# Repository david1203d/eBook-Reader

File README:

# 📘 Ebook Reader cu ESP32-C6

Acest proiect este un **Ebook Reader portabil**, cu consum redus, bazat pe **ESP32-C6** și ecran **E-Paper**, ideal pentru lectură prelungită.  
Dispozitivul citește fișiere `.txt` de pe un card **microSD** și permite navigarea cu **butoane fizice**, având alimentare din **baterie Li-Po** și opțional monitorizare a nivelului acesteia.

---

## 📦 Bill of Materials (BOM)

| Componentă           | Model/Tip                  | Link comandă | Datasheet     |
|----------------------|----------------------------|--------------|----------------|
| Microcontroller      | ESP32-C6                   | Mouser       | [ESP32-C6](#)  |
| Ecran                | E-Paper Display 2.9"       | Comet        | [GDEH029A1](#) |
| Cart Reader          | MicroSD SPI module         | Mouser       | [Modul SD](#)  |
| Senzor de mediu      | BME688                     | Mouser       | [BME688](#)    |
| RTC                  | DS3231SN                   | Mouser       | [DS3231](#)    |
| Battery Monitor      | MAX17048                   | Mouser       | [MAX17048](#)  |
| Flash extern         | W25Q512JV (64MB)           | Mouser       | [W25Q512JV](#) |
| Regulator tensiune   | MCP1826S-3302E/DB          | Mouser       | [MCP1826](#)   |
| BMS                  | TP4056                     | Comet        | [TP4056](#)    |
| Butoane              | Tactile Switches           | Comet        | [SKQG](#)      |

---

## ⚙️ Funcționalitate Hardware

### 1. ESP32-C6
- Interfață principală: SPI, I2C, GPIO  
- Flash extern NOR (64MB) prin QSPI  
- UART pentru debug  
- Alimentare 3.3V prin LDO

### 2. E-Paper Display
- Alimentat prin EPD Power Driver (boost + FET)  
- Conectat prin SPI la ESP32-C6  
- Pini dedicați: DIN, CLK, CS, DC, RST, BUSY

### 3. Modul SD Card
- Interfață SPI  
- Stocare fișiere `.txt`

### 4. RTC DS3231SN
- I2C cu backup battery (CR2032)  
- Oră exactă cu temperatură compensată

### 5. Senzor BME688
- I2C – temperatură, presiune, umiditate, calitate aer  
- Util pentru monitorizare ambientală (opțional)

### 6. MAX17048
- Monitorizare nivel baterie prin I2C  
- Poate afișa procentul pe ecran

### 7. TP4056 Charging
- Încărcare Li-Po prin USB-C  
- Protecție la supradescărcare/supraincărcare

---

## 📌 Pini ESP32-C6 Utilizați

| Pin ESP32-C6 | Funcție hardware         | Componentă              |
|--------------|--------------------------|--------------------------|
| GPIO0        | I2C SCL                  | BME688, MAX17048, DS3231 |
| GPIO1        | I2C SDA                  | BME688, MAX17048, DS3231 |
| GPIO2        | SPI MOSI                | E-paper, SD, Flash       |
| GPIO3        | SPI MISO                | SD, Flash                |
| GPIO4        | SPI CLK                 | E-paper, SD, Flash       |
| GPIO5        | SPI CS (e-paper)        | E-paper                  |
| GPIO6        | SPI CS (SD card)        | SD Card                  |
| GPIO7        | SPI CS (Flash extern)   | W25Q512JV                |
| GPIO8        | GPIO Buton 1            | Pag. înainte             |
| GPIO9        | GPIO Buton 2            | Pag. înapoi              |
| GPIO10       | GPIO Buton 3            | Reset/Menu               |
| GPIO11       | UART TX                 | Debug UART               |
| GPIO12       | UART RX                 | Debug UART               |

---

## 🖼️ Design PCB & Randări

- **PCB**: 2 straturi, dimensiuni: `92.2mm x 67.2mm`  
- **Componente** poziționate compact pentru portabilitate  
- **Acces ușor** la card microSD, USB-C și butoane  
- **Protecție ESD** pe liniile USB și SPI  

## ✅ Alte Detalii Relevante

- **Mod Deep Sleep**: activat după 30s de inactivitate  
- **W25Q512JV Flash extern**: stocare rapidă pentru sute de cărți `.txt`  
- **Qwiic/Stemma QT header**: pentru expansiune cu alte periferice  
- **Test Pads**: depanare & validare semnal

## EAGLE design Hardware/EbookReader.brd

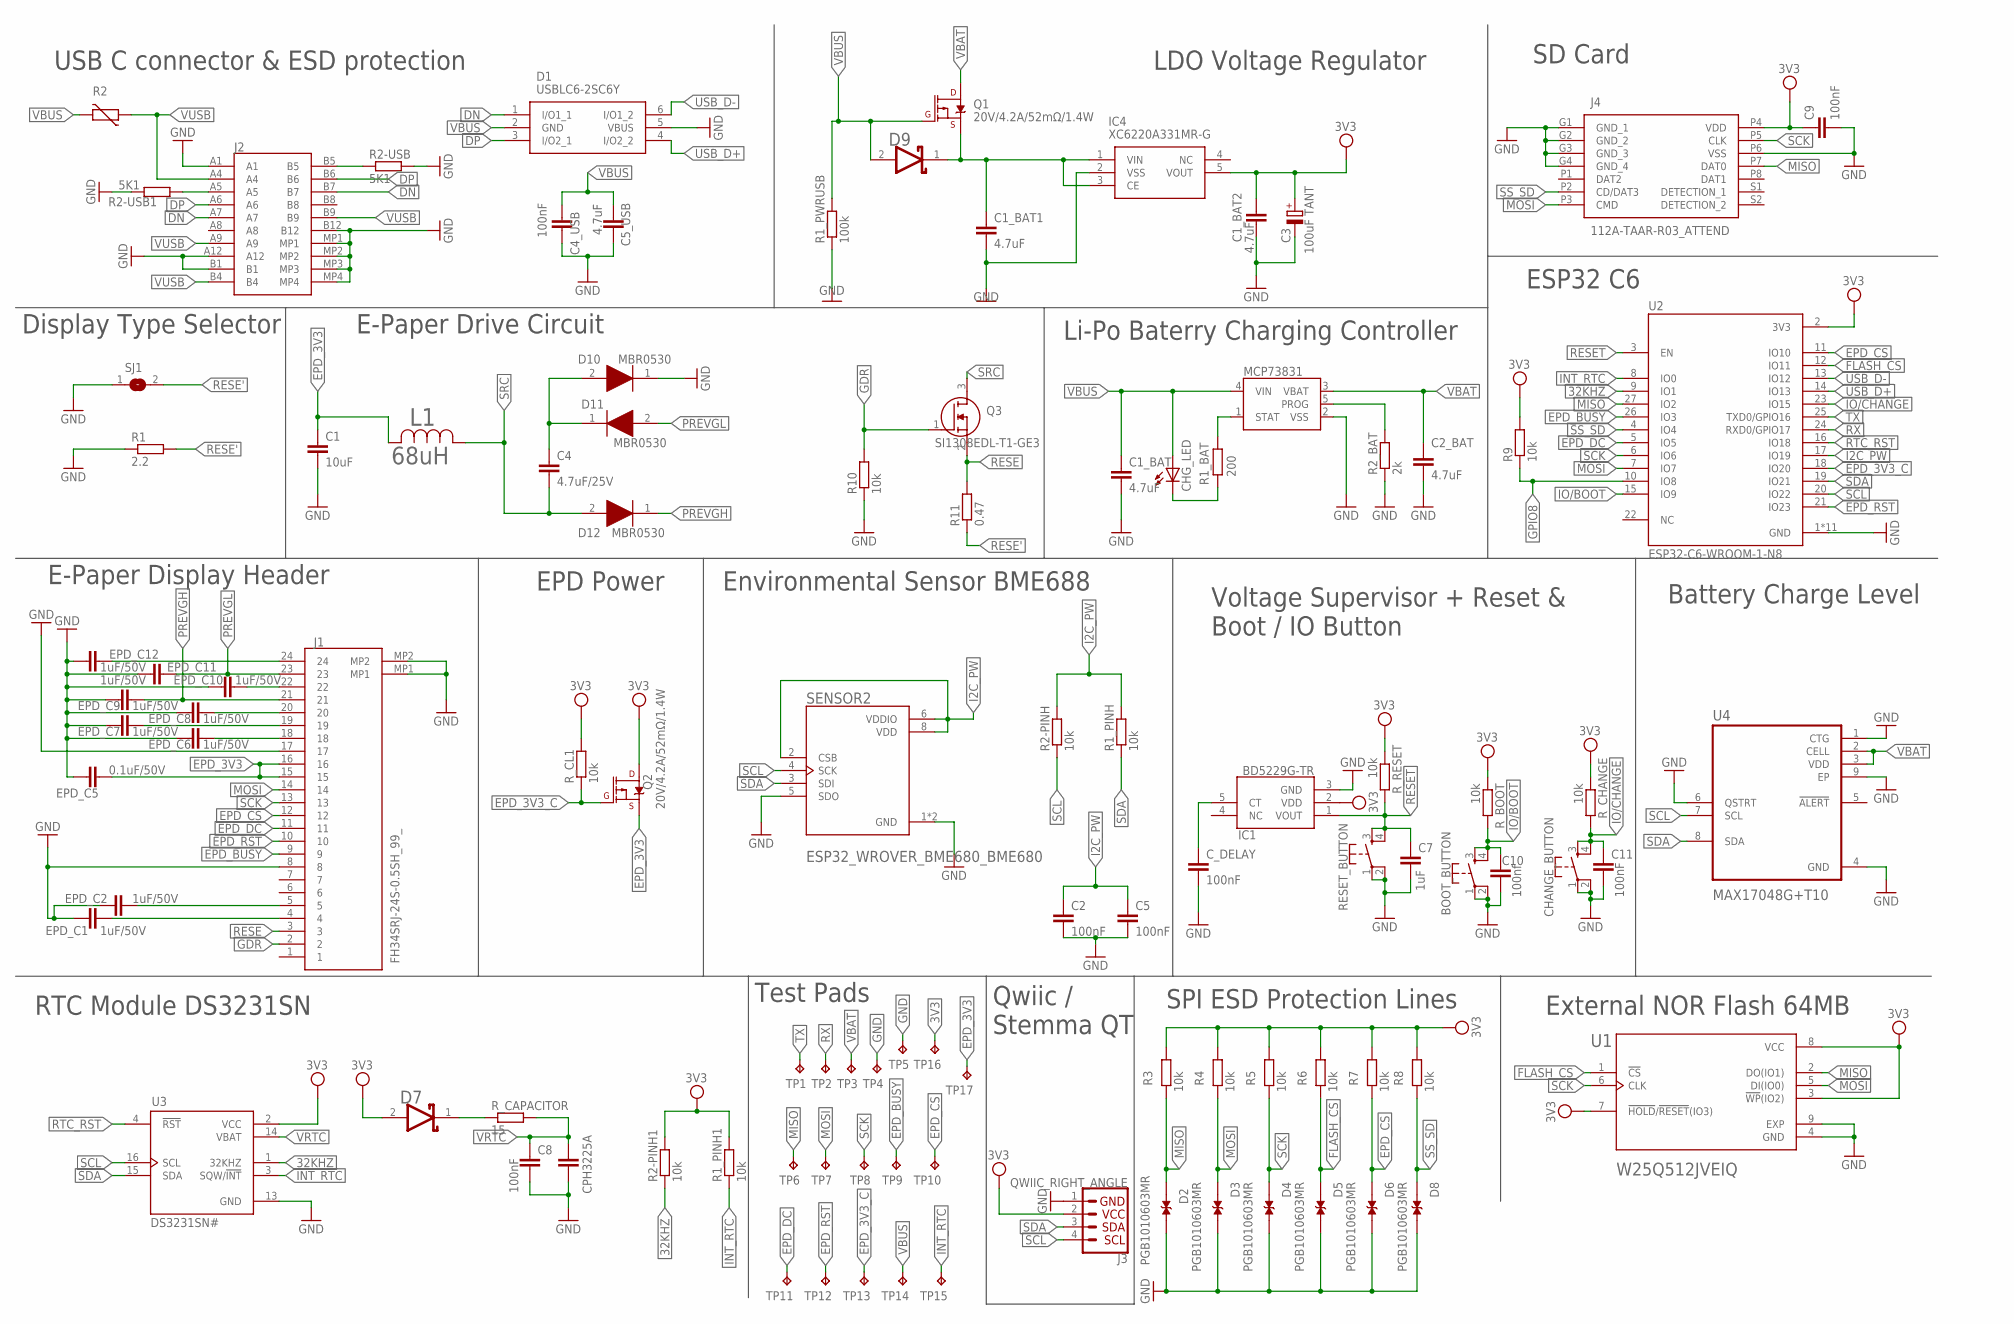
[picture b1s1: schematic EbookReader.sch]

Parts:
BOOT_BUTTON: BUTTON_CUSYOMV1; MYBUTTON
C1: 10uF; ESP32_WROVER_EAGLE-LTSPICE_C0402
C1_BAT, C1_BAT1, C1_BAT2, C2_BAT, C5_USB: 4.7uF; ESP32_WROVER_EAGLE-LTSPICE_C0402
C2, C4_USB, C5, C9, C11: 100nF; ESP32_WROVER_EAGLE-LTSPICE_C0402
C3: 100uF TANT; RCL_CT3528
C4: 4.7uF/25V; ESP32_WROVER_EAGLE-LTSPICE_C0402
C7: 1uF; ESP32_WROVER_EAGLE-LTSPICE_C0402
C8: 100nF; EAGLE-LTSPICE_C0402
C10: 100nf; ESP32_WROVER_EAGLE-LTSPICE_C0402
CHANGE_BUTTON: BUTTON_CUSYOMV1; MYBUTTON
CHG_LED: ADAFRUIT_LEDCHIP-LED0603; ADAFRUIT_CHIP-LED0603
CPH3225A: EAGLE-LTSPICE_CC0402; EAGLE-LTSPICE_C0402
C_DELAY: 100nF; ESP32_WROVER_EAGLE-LTSPICE_C0402
D1: USBLC6-2SC6Y; SOT95P280X145-6N
D2, D3, D4, D5, D6, D8: PGB1010603MR; DIOC1608X36N
D7, D9: ESP32_WROVER_AVX---SD0805S020S1R0_AVX_SD0805S020S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; ESP32_WROVER_AVX---SD0805S020S1R0_AVX_SD0805S020S1R0_0
D10, D11, D12: MBR0530; SOD3716X135N
EPD_C1, EPD_C2, EPD_C6, EPD_C7, EPD_C8, EPD_C9, EPD_C10, EPD_C11, EPD_C12: 1uF/50V; EAGLE-LTSPICE_C0402
EPD_C5: 0.1uF/50V; EAGLE-LTSPICE_C0402
IC1: BD5229G-TR; SOT95P280X125-5N
IC4: XC6220A331MR-G; SOT95P280X120-5N
J1: FH34SRJ-24S-0.5SH_99_; FH34SRJ24S05SH99
J2: SAMACSYS_PARTS_USB4110-GF-A; SAMACSYS_PARTS_USB4110GFA
J3: QWIIC_RIGHT_ANGLE; JST04_1MM_RA
J4: 112A-TAAR-R03_ATTEND; 112ATAARR03ATTEND
L1: 68uH; IND_4828-WE-TPC_WRE
MCP73831: ESP32_WROVER_SPARKFUN-IC-POWER_MCP73831; ESP32_WROVER_SPARKFUN-IC-POWER_SOT23-5
Q1, Q2: 20V/4.2A/52mΩ/1.4W; ESP32_WROVER_SPARKFUN-DISCRETESEMI_SOT23-3
Q3: SI1308EDL-T1-GE3; SOT65P210X110-3N
R1: 2.2; ESP32_WROVER_EAGLE-LTSPICE_R0402
R1_BAT: 200; ESP32_WROVER_EAGLE-LTSPICE_R0402
R1_PINH, R1_PINH1, R2-PINH, R2-PINH1, R3, R4, R5, R6, R7, R8, R9, R10: 10k; ESP32_WROVER_EAGLE-LTSPICE_R0402
R1_PWRUSB: 100k; ESP32_WROVER_EAGLE-LTSPICE_R0402
R2: ESP32C6_VARISTORCN1812; ESP32C6_VARISTOR_CT/CN1812
R2-USB, R2-USB1: 5K1; ESP32_WROVER_EAGLE-LTSPICE_R0402
R2_BAT: 2k; ESP32_WROVER_EAGLE-LTSPICE_R0402
R11: 0.47; ESP32_WROVER_EAGLE-LTSPICE_R0402
RESET_BUTTON: BUTTON_CUSYOMV1; MYBUTTON
R_BOOT: 10k; ESP32_WROVER_EAGLE-LTSPICE_R0402
R_CAPACITOR: 15; ESP32_WROVER_EAGLE-LTSPICE_R0402
R_CHANGE: 10k; ESP32_WROVER_EAGLE-LTSPICE_R0402
R_CL1: 10k; ESP32_WROVER_EAGLE-LTSPICE_R0402
R_RESET: 10k; ESP32_WROVER_EAGLE-LTSPICE_R0402
SENSOR2: ESP32_WROVER_BME680_BME680; ESP32_WROVER_BME680_PSON80P300X300X100-8N
SJ1: SJ
TP1, TP2, TP3, TP4, TP5, TP6, TP7, TP8, TP9, TP10, TP11, TP12, TP13, TP14, TP15, TP16, TP17: TPTP20R; TP20R
U1: W25Q512JVEIQ; SON127P600X800X80-9N
U2: ESP32-C6-WROOM-1-N8; XCVR_ESP32-C6-WROOM-1-N8
U3: DS3231SN#; SOIC127P1032X265-16N
U4: MAX17048G+T10; SON50P200X200X80-9N

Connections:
3V3: C1_BAT2.1, C3.+, C9.1, D7.2 (ANODE), IC1.2 (VDD), IC4.5 (VOUT), J3.2, J4.P4 (VDD), Q2.3 (D), R1_PINH1.2, R2-PINH1.2, R3.2, R4.2, R5.2, R6.2, R7.2, R8.2, R9.2, R_BOOT.1, R_CHANGE.1, R_CL1.2, R_RESET.1, TP16.TP, U1.3 (!WP!(IO2)), U1.7 (!HOLD!/!RESET!(IO3)), U1.8 (VCC), U2.2 (3V3), U3.2 (VCC)
32KHZ: R2-PINH1.1, U2.9 (IO1), U3.1 (32KHZ)
DN: D1.1 (I/O1_1), J2.A7, J2.B7
DP: D1.3 (I/O2_1), J2.A6, J2.B6
EPD_3V3: C1.1, EPD_C5.1, J1.15, J1.16, L1.2, Q2.2 (S), TP17.TP
EPD_3V3_C: Q2.1 (G), R_CL1.1, TP13.TP, U2.18 (IO20)
EPD_BUSY: J1.9, TP9.TP, U2.26 (IO3)
EPD_CS: D6.1, J1.12, R7.1, TP10.TP, U2.11 (IO10)
EPD_DC: J1.11, TP11.TP, U2.5 (IO5)
EPD_RST: J1.10, TP12.TP, U2.21 (IO23)
FLASH_CS: D5.1, R6.1, U1.1 (!CS), U2.12 (IO11)
GDR: J1.2, Q3.1 (G), R10.2
GND: BOOT_BUTTON.1, BOOT_BUTTON.2, C1.2, C1_BAT.2, C1_BAT1.2, C1_BAT2.2, C2.2, C2_BAT.2, C3.-, C4_USB.2, C5.2, C5_USB.2, C7.2, C8.2, C9.2, C10.2, C11.2, CHANGE_BUTTON.1, CHANGE_BUTTON.2, CPH3225A.2, C_DELAY.2, D1.5 (VBUS), D2.2, D3.2, D4.2, D5.2, D6.2, D8.2, D10.1 (K), EPD_C1.2, EPD_C2.2, EPD_C5.2, EPD_C6.2, EPD_C7.2, EPD_C8.2, EPD_C9.2, EPD_C10.2, EPD_C11.2, EPD_C12.2, IC1.3 (GND), IC4.2 (VSS), J1.8, J1.17, J1.MP1, J1.MP2, J2.A1, J2.A12, J2.B1, J2.B12, J2.MP1, J2.MP2, J2.MP3, J2.MP4, J3.1, J4.G1 (GND_1), J4.G2 (GND_2), J4.G3 (GND_3), J4.G4 (GND_4), J4.P6 (VSS), MCP73831.2 (VSS), R1.1, R1_PWRUSB.1, R2-USB.2, R2-USB1.1, R2_BAT.1, R10.1, RESET_BUTTON.1, RESET_BUTTON.2, SENSOR2.1 (GND), SENSOR2.5 (SDO), SENSOR2.7 (GND), SJ1.1, TP4.TP, TP5.TP, U1.4 (GND), U1.9 (EXP), U2.1 (GND), U2.28 (GND), U2.29_1 (GND), U2.29_2 (GND), U2.29_3 (GND), U2.29_4 (GND), U2.29_5 (GND), U2.29_6 (GND), U2.29_7 (GND), U2.29_8 (GND), U2.29_9 (GND), U3.13 (GND), U4.1 (CTG), U4.4 (GND), U4.6 (QSTRT), U4.9 (EP)
GPIO8: R9.1, U2.10 (IO8)
I2C_PW: C2.1, C5.1, R1_PINH.2, R2-PINH.2, SENSOR2.2 (CSB), SENSOR2.6 (VDDIO), SENSOR2.8 (VDD), U2.17 (IO19)
INT_RTC: R1_PINH1.1, TP15.TP, U2.8 (IO0), U3.3 (SQW/!INT)
IO/BOOT: BOOT_BUTTON.3, BOOT_BUTTON.4, C10.1, R_BOOT.2, U2.15 (IO9)
IO/CHANGE: C11.1, CHANGE_BUTTON.3, CHANGE_BUTTON.4, R_CHANGE.2, U2.23 (IO15)
MISO: D2.1, J4.P7 (DAT0), R3.1, TP6.TP, U1.2 (DO(IO1)), U2.27 (IO2)
MOSI: D3.1, J1.14, J4.P3 (CMD), R4.1, TP7.TP, U1.5 (DI(IO0)), U2.7 (IO7)
unnamed: J2.A5, R2-USB1.2
unnamed: EPD_C12.1, J1.24
unnamed: D7.1 (CATHODE), R_CAPACITOR.1
unnamed: EPD_C10.1, J1.22
unnamed: EPD_C8.1, J1.20
unnamed: MCP73831.5 (PROG), R2_BAT.2
unnamed: EPD_C7.1, J1.19
unnamed: EPD_C6.1, J1.18
unnamed: J2.B5, R2-USB.1
unnamed: MCP73831.1 (STAT), R1_BAT.1
unnamed: EPD_C2.1, J1.5
unnamed: EPD_C1.1, J1.4
unnamed: C4.1, D10.2 (A), D11.1 (K)
unnamed: CHG_LED.C, R1_BAT.2
unnamed: C_DELAY.1, IC1.5 (CT)
unnamed: C1_BAT1.1, D9.1 (CATHODE), IC4.1 (VIN), IC4.3 (CE), Q1.2 (S)
PREVGH: D12.1 (K), EPD_C9.1, J1.21
PREVGL: D11.2 (A), EPD_C11.1, J1.23
RESE: J1.3, Q3.2 (S), R11.2
RESE': R1.2, R11.1, SJ1.2
RESET: C7.1, IC1.1 (VOUT), RESET_BUTTON.3, RESET_BUTTON.4, R_RESET.2, U2.3 (EN)
RTC_RST: U2.16 (IO18), U3.4 (!RST)
RX: TP2.TP, U2.24 (RXD0/GPIO17)
SCK: D4.1, J1.13, J4.P5 (CLK), R5.1, TP8.TP, U1.6 (CLK), U2.6 (IO6)
SCL: J3.4, R2-PINH.1, SENSOR2.4 (SCK), U2.20 (IO22), U3.16 (SCL), U4.7 (SCL)
SDA: J3.3, R1_PINH.1, SENSOR2.3 (SDI), U2.19 (IO21), U3.15 (SDA), U4.8 (SDA)
SRC: C4.2, D12.2 (A), L1.1, Q3.3 (D)
SS_SD: D8.1, J4.P2 (CD/DAT3), R8.1, U2.4 (IO4)
TX: TP1.TP, U2.25 (TXD0/GPIO16)
USB_D+: D1.4 (I/O2_2), U2.14 (IO13)
USB_D-: D1.6 (I/O1_2), U2.13 (IO12)
VBAT: C2_BAT.1, MCP73831.3 (VBAT), Q1.3 (D), TP3.TP, U4.2 (CELL), U4.3 (VDD)
VBUS: C1_BAT.1, C4_USB.1, C5_USB.1, CHG_LED.A, D1.2 (GND), D9.2 (ANODE), MCP73831.4 (VIN), Q1.1 (G), R1_PWRUSB.2, R2.2, TP14.TP
VRTC: C8.1, CPH3225A.1, R_CAPACITOR.2, U3.14 (VBAT)
VUSB: J2.A4, J2.A9, J2.B4, J2.B9, R2.1

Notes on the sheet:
USB C connector & ESD protection
LDO Voltage Regulator
Display Type Selector
E-Paper Drive Circuit
Li-Po Baterry Charging Controller
E-Paper Display Header
RTC Module DS3231SN
EPD Power
Test Pads
Environmental Sensor BME688
Qwiic / Stemma QT
SPI ESD Protection Lines
Voltage Supervisor + Reset & Boot / IO Button
Battery Charge Level
External NOR Flash 64MB
ESP32 C6
SD Card

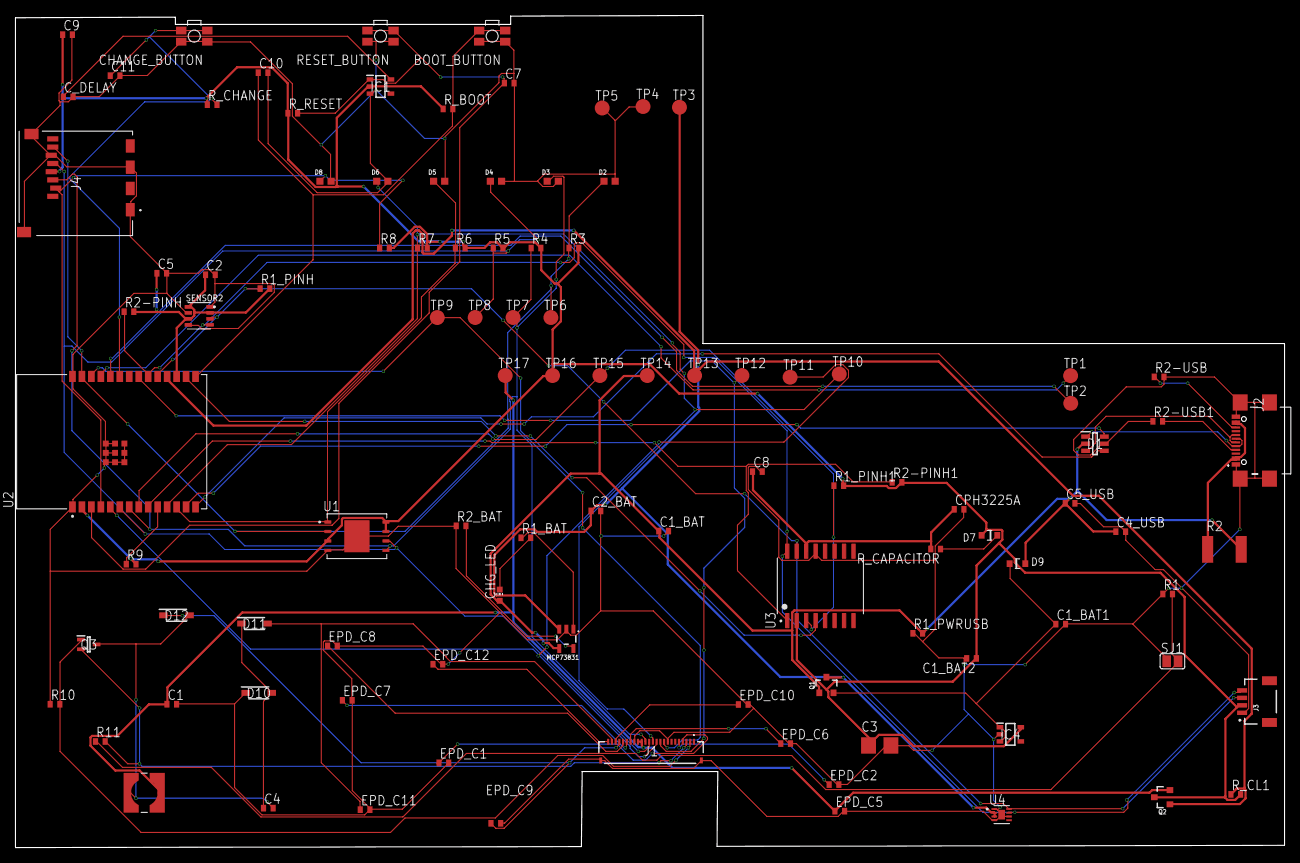
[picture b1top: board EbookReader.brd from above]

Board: 2 copper layers, 170.2 x 111.6 mm, 103 parts (0 on the bottom side), 55 nets.

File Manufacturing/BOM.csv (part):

Qty,Value,Device,Package,Parts,Description,ARROW_PART_NUMBER,ARROW_PRICE-STOCK,AVAILABILITY,CENTROID_NOT_SPECIFIED,CHECK_PRICES,COPYRIGHT,DATASHEET,DESCRIPTION,DIGIKEY_DESCRIPTION,DIGIKEY_PART_NUMBER,HEIGHT,LEAD_FREE,MANUFACTURER_NAME,MANUFACTURER_PART_NUMBER,MF,MFR_NAME,MOUSER_PART_NUMBER,MOUSER_PRICE-STOCK,MOUSER_TESTING_PART_NUMBER,MOUSER_TESTING_PRICE-STOCK,MP,MPN,PACKAGE,POPULARITY,PREFIX,PRICE,PROD_ID,PURCHASE-URL,ROHS,SNAPEDA_LINK,SPICEMODEL,SPICEPREFIX,TEMPERATURE_RANGE_HIGH,TEMPERATURE_RANGE_LOW,TP_SIGNAL_NAME,VALUE
1,,ADAFRUIT_LEDCHIP-LED0603,ADAFRUIT_CHIP-LED0603,CHG_LED,LED,,,,,,,,,,,,,,,,,,,,,,,,,,,,,,,,,,,,
1,,EAGLE-LTSPICE_CC0402,EAGLE-LTSPICE_C0402,CPH3225A,"CAPACITOR, European symbol",,,,,,,,,,,,,,,,,,,,,,,,,,,,,,,NONE,C,,,,
1,,SJ,SJ,SJ1,"SMD solder JUMPER",,,,,,,,,,,,,,,,,,,,,,,,3,,,,,,,,,,,,
1,0.1uF/50V,EAGLE-LTSPICE_CC0402,EAGLE-LTSPICE_C0402,EPD_C5,"CAPACITOR, European symbol",,,,,,,,,,,,,,,,,,,,,,,,,,,,,,,NONE,C,,,,
1,0.47,ESP32_WROVER_EAGLE-LTSPICE_RR0402,ESP32_WROVER_EAGLE-LTSPICE_R0402,R11,"RESISTOR, European symbol",,,,,,,,,,,,,,,,,,,,,,,,,,,,,,,NONE,R,,,,
1,100k,ESP32_WROVER_EAGLE-LTSPICE_RR0402,ESP32_WROVER_EAGLE-LTSPICE_R0402,R1_PWRUSB,"RESISTOR, European symbol",,,,,,,,,,,,,,,,,,,,,,,,,,,,,,,NONE,R,,,,
1,100nF,EAGLE-LTSPICE_CC0402,EAGLE-LTSPICE_C0402,C8,"CAPACITOR, European symbol",,,,,,,,,,,,,,,,,,,,,,,,,,,,,,,NONE,C,,,,
6,100nF,ESP32_WROVER_EAGLE-LTSPICE_CC0402,ESP32_WROVER_EAGLE-LTSPICE_C0402,"C2, C4_USB, C5, C9, C11, C_DELAY","CAPACITOR, European symbol",,,,,,,,,,,,,,,,,,,,,,,,,,,,,,,NONE,C,,,,
1,100nf,ESP32_WROVER_EAGLE-LTSPICE_CC0402,ESP32_WROVER_EAGLE-LTSPICE_C0402,C10,"CAPACITOR, European symbol",,,,,,,,,,,,,,,,,,,,,,,,,,,,,,,NONE,C,,,,
1,"100uF TANT",RCL_CPOL-EUCT3528,RCL_CT3528,C3,"POLARIZED CAPACITOR, European symbol",,,,,,,,,,,,,,,,,,,,,,,,0,,,,,,,,C,,,,
16,10k,ESP32_WROVER_EAGLE-LTSPICE_RR0402,ESP32_WROVER_EAGLE-LTSPICE_R0402,"R1_PINH, R1_PINH1, R2-PINH, R2-PINH1, R3, R4, R5, R6, R7, R8, R9, R10, R_BOOT, R_CHANGE, R_CL1, R_RESET","RESISTOR, European symbol",,,,,,,,,,,,,,,,,,,,,,,,,,,,,,,NONE,R,,,,
1,10uF,ESP32_WROVER_EAGLE-LTSPICE_CC0402,ESP32_WROVER_EAGLE-LTSPICE_C0402,C1,"CAPACITOR, European symbol",,,,,,,,,,,,,,,,,,,,,,,,,,,,,,,NONE,C,,,,
1,112A-TAAR-R03_ATTEND,112A-TAAR-R03_ATTEND,112ATAARR03ATTEND,J4,"Micro SD Card Socket, Push-Push Type, Top Mount, SMT, H=1.83mm, 10u",,,,,,,,"Micro SD Card Socket"," Push-Push Type"," Top Mount"," SMT"," H=1.83mm"," 10u",,,1.9mm,,ATTEND,"112A-TAAR-R03 ATTEND",,,,,,,,,,,,,,,,,
1,15,ESP32_WROVER_EAGLE-LTSPICE_RR0402,ESP32_WROVER_EAGLE-LTSPICE_R0402,R_CAPACITOR,"RESISTOR, European symbol",,,,,,,,,,,,,,,,,,,,,,,,,,,,,,,NONE,R,,,,
1,1uF,ESP32_WROVER_EAGLE-LTSPICE_CC0402,ESP32_WROVER_EAGLE-LTSPICE_C0402,C7,"CAPACITOR, European symbol",,,,,,,,,,,,,,,,,,,,,,,,,,,,,,,NONE,C,,,,
9,1uF/50V,EAGLE-LTSPICE_CC0402,EAGLE-LTSPICE_C0402,"EPD_C1, EPD_C2, EPD_C6, EPD_C7, EPD_C8, EPD_C9, EPD_C10, EPD_C11, EPD_C12","CAPACITOR, European symbol",,,,,,,,,,,,,,,,,,,,,,,,,,,,,,,NONE,C,,,,
1,2.2,ESP32_WROVER_EAGLE-LTSPICE_RR0402,ESP32_WROVER_EAGLE-LTSPICE_R0402,R1,"RESISTOR, European symbol",,,,,,,,,,,,,,,,,,,,,,,,,,,,,,,NONE,R,,,,
1,200,ESP32_WROVER_EAGLE-LTSPICE_RR0402,ESP32_WROVER_EAGLE-LTSPICE_R0402,R1_BAT,"RESISTOR, European symbol",,,,,,,,,,,,,,,,,,,,,,,,,,,,,,,NONE,R,,,,
2,20V/4.2A/52mO/1.4W,ESP32_WROVER_SPARKFUN-DISCRETESEMI_MOSFET_PCH-DMG2305UX-7,ESP32_WROVER_SPARKFUN-DISCRETESEMI_SOT23-3,"Q1, Q2","P-channel MOSFETs",,,,,,,,,,,,,,,,,,,,,,,,,,,TRAN-14388,,,,,,,,,20V/4.2A/52mO/1.4W
1,2k,ESP32_WROVER_EAGLE-LTSPICE_RR0402,ESP32_WROVER_EAGLE-LTSPICE_R0402,R2_BAT,"RESISTOR, European symbol",,,,,,,,,,,,,,,,,,,,,,,,,,,,,,,NONE,R,,,,
5,4.7uF,ESP32_WROVER_EAGLE-LTSPICE_CC0402,ESP32_WROVER_EAGLE-LTSPICE_C0402,"C1_BAT, C1_BAT1, C1_BAT2, C2_BAT, C5_USB","CAPACITOR, European symbol",,,,,,,,,,,,,,,,,,,,,,,,,,,,,,,NONE,C,,,,
1,4.7uF/25V,ESP32_WROVER_EAGLE-LTSPICE_CC0402,ESP32_WROVER_EAGLE-LTSPICE_C0402,C4,"CAPACITOR, European symbol",,,,,,,,,,,,,,,,,,,,,,,,,,,,,,,NONE,C,,,,
2,5K1,ESP32_WROVER_EAGLE-LTSPICE_RR0402,ESP32_WROVER_EAGLE-LTSPICE_R0402,"R2-USB, R2-USB1","RESISTOR, European symbol",,,,,,,,,,,,,,,,,,,,,,,,,,,,,,,NONE,R,,,,
1,68uH,744043680IND_4828-WE-TPC_WRE,IND_4828-WE-TPC_WRE,L1,,,,,,,"Copyright (C) 2024 Ultra Librarian. All rights reserved.",,,,,,,,744043680,,"Wurth Electronics",,,,,,,,,,,,,,,,,,,,
1,BD5229G-TR,BD5229G-TR,SOT95P280X125-5N,IC1,"Voltage Detector with Adjustable Delay Time: CMOS processes are utilized to develop high precision, low current consumption CMOS reset ICs that allow arbitrary setting of the delay time. The extensive lineup includes both Nch Open Drain and CMOS output types in a wide range of detection voltages (from 2.3V to 6.0V, in 0.1V steps), enabling selection of the ideal solution based on customer requirements. In addition, the entire series is of course both lead-free and RoHS-compliant.",,,,,,,,"Voltage Detector with Adjustable Delay Time: CMOS processes are utilized to develop high precision"," low current consumption CMOS reset ICs that allow arbitrary setting of the delay time. The extensive lineup includes both Nch Open Drain and CMOS output types in a wide range of detection voltages (from 2.3V to 6.0V"," in 0.1V steps)"," enabling selection of the ideal solution based on customer requirements. In addition"," the entire series is of course both lead-free and RoHS-compliant.",,,1.25mm,,"ROHM Semiconductor",BD5229G-TR,,,755-BD5229G-TR,https://www.mouser.co.uk/ProductDetail/ROHM-Semiconductor/BD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,,,,,,,,,,,,,,
3,BUTTON_CUSYOMV1,BUTTON_CUSYOMV1,MYBUTTON,"BOOT_BUTTON, CHANGE_BUTTON, RESET_BUTTON",,,,,,,,,,,,,,,,,,,,,,,,,,,,,,,,,,,,,
1,DS3231SN#,DS3231SN#,SOIC127P1032X265-16N,U3,"Real Time Clock Serial 16-Pin SOIC W T/R     Check availability",,,"In Stock",,https://www.snapeda.com/parts/DS3231SN%23/Analog+Devices/vie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,,," Extremely Accurate I²C-Integrated RTC/TCXO/Crystal ",,,,,,,"Analog Devices",,,,,,DS3231SN#,,"SOIC-16 Maxim",,,None,,"https://www.snapeda.com/api/url_track_click_mouser/?unipart_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 Devices&part_name=DS3231SN#&search_term=None",,https://www.snapeda.com/parts/DS3231SN%23/Analog+Devices/vie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,,,,,,
1,ESP32-C6-WROOM-1-N8,ESP32-C6-WROOM-1-N8,XCVR_ESP32-C6-WROOM-1-N8,U2,"Check availability",,,"In Stock",,https://www.snapeda.com/parts/ESP32-C6-WROOM-1-N8/Espressif+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,,," Multiprotocol Modules ESP32-C6 module"," Wi-Fi 6 in 2.4 GHz band"," Bluetooth 5"," Zigbee 3.0 and Thread. ESP34-WROOM Compatible - ENGINEERING SAMPLE ",,,,,,,"Espressif Systems",,,,,,ESP32-C6-WROOM-1-N8,,None,,,None,,,,https://www.snapeda.com/parts/ESP32-C6-WROOM-1-N8/Espressif+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,,,
1,ESP32C6_VARISTORCN1812,ESP32C6_VARISTORCN1812,ESP32C6_VARISTOR_CT/CN1812,R2,VARISTOR,,,,,,,,,,,,,,,,,,,,,,,,0,,,,,,,,,,,,
2,ESP32_WROVER_AVX---SD0805S020S1R0_AVX_SD0805S020S1R0_0_0AVX_SD0805S020S1R0_0_0,ESP32_WROVER_AVX---SD0805S020S1R0_AVX_SD0805S020S1R0_0_0AVX_SD0805S020S1R0_0_0,ESP32_WROVER_AVX---SD0805S020S1R0_AVX_SD0805S020S1R0_0,"D7, D9","Schottky Barrier Rectifier Diode",,,,No,,,http://datasheets.avx.com/schottky.pdf,,"DIODE SCHOTTKY 20V 1A 0805",478-7800-1-ND,,yes,,,AVX,,581-SD0805S020S1R0,,,,,,"0805 (2012 metric)",,D,,,,yes,,,,+125°C,-55°C,,
1,ESP32_WROVER_BME680_BME680,ESP32_WROVER_BME680_BME680,ESP32_WROVER_BME680_PSON80P300X300X100-8N,SENSOR2,"Integrated Environmental Unit",,,Unavailable,,,,," Integrated Environmental Unit ",,,,,,,"Bosch Sensortec",,,,,,BME680,,"LGA-8 Bosch Tools",,,None,,,,,,,,,,
1,ESP32_WROVER_SPARKFUN-IC-POWER_MCP73831,ESP32_WROVER_SPARKFUN-IC-POWER_MCP73831,ESP32_WROVER_SPARKFUN-IC-POWER_SOT23-5,MCP73831,"MCP73831T Li-Ion, Li-Pol Controller",,,,,,,,,,,,,,,,,,,,,,,,,,,IC-09995,,,,,,,,,
1,FH34SRJ-24S-0.5SH_99_,FH34SRJ-24S-0.5SH_99_,FH34SRJ24S05SH99,J1," (0.50mm) Surface Mount, Right Angle",,,,,,,,"24 Position FFC"," FPC Connector Contacts"," (0.50mm) Surface Mount"," Right Angle",,,1.1mm,,Hirose,FH34SRJ-24S-0.5SH(99),,,798-FH34SRJ24S05SH99,https://www.mouser.co.uk/ProductDetail/Hirose-Connector/FH34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,,,,,,,,,,,,,,,
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
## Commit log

2025-04-06 Adaug fisiere hardware
2025-04-06 Create LICENSE
2025-04-06 Rename README to README.md

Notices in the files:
parts and their libraries:
COPYRIGHT: Copyright (C) 2024 Ultra Librarian. All rights reserved.
